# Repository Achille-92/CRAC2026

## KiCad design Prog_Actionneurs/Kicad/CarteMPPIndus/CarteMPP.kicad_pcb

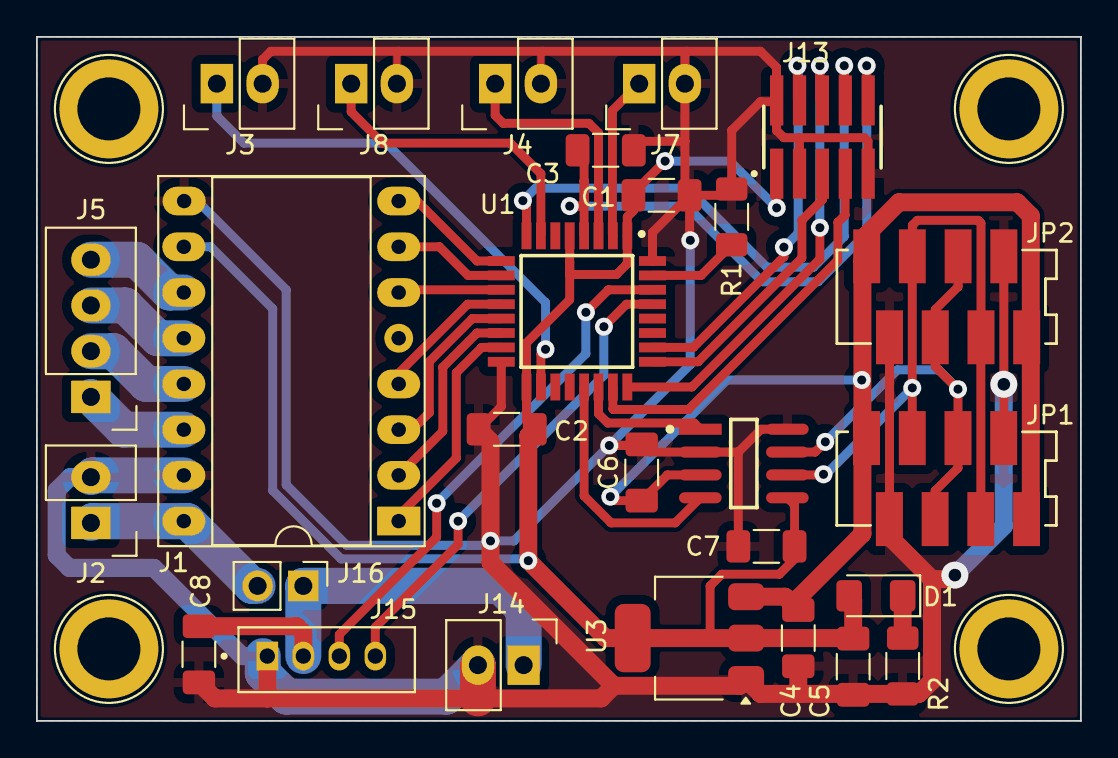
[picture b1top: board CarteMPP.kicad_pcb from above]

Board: 2 copper layers, 58.0 x 38.0 mm, 31 parts (0 on the bottom side), 34 nets.

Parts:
C1, C2, C3, C6, C7: 100nF; C_1206_3216Metric_Pad1.33x1.80mm_HandSolder
C4: 10uF; C_1206_3216Metric_Pad1.33x1.80mm_HandSolder
C5: 22uF; C_1206_3216Metric_Pad1.33x1.80mm_HandSolder
C8: Cap; C_1206_3216Metric_Pad1.33x1.80mm_HandSolder
D1: LED; LED_1206_3216Metric_Pad1.42x1.75mm_HandSolder
J1: Conn_01x08; DIP-16_W7.62mm_Socket_LongPads
J2, J3, J4, J7, J8, J14: Autocom2
J5: Autocom4
J9, J10, J11, J12: Mounting_Screw_3mm
J13: FTSH-105-01-L-DV-K; SAMTEC_FTSH-105-01-L-DV-K
J15: Conn_01x02; PinHeader_1x02_P2.54mm_Vertical
J16: Herkulex; TE_292161-4
JP1, JP2: Micromatch 8; SW_DIP_SPSTx04_Slide_9.78x12.34mm_W7.62mm_P2.54mm
R1: 10K; R_1206_3216Metric_Pad1.30x1.75mm_HandSolder
R2: 360; R_1206_3216Metric_Pad1.30x1.75mm_HandSolder
U1: STM32F303K8T6; QFP80P900X900X160-32N
U2: MCP2562FDT-E/SN; SW_DIP_SPSTx02_Slide_9.78x7.26mm_W7.62mm_P2.54mm
U3: AZ1117-3.3; SOT-223-3_TabPin2

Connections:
+3.3V: C1.2, C2.2, C5.1, C7.1, D1.2 (A), J1.10 (Pin_2), J13.01, U1.1 (VDD3), U1.5 (VDDA/VREF+), U1.17 (VDD2/VDD_USB), U2.5 (VIO), U3.2 (VO)
+5V: C4.1, C6.1, JP1.1 (VCC), JP1.8 (VCC), JP2.1 (VCC), JP2.8 (VCC), U2.3 (VDD), U3.3 (VI)
/A1: J1.12 (Pin_4), J5.3
/A2: J1.11 (Pin_3), J5.4
/Aux1: J8.1, U1.7 (PA1)
/Aux2: J3.1, U1.18 (PA8)
/Aux3: J4.1, U1.3 (PF1/PC15)
/Aux4: J7.1, U1.2 (PF0/PC14)
/B1: J1.14 (Pin_6), J5.1
/B2: J1.13 (Pin_5), J5.2
/BOOT0: R1.2, U1.31 (BOOT0/PB8/PH3)
/CAN_H: JP1.4 (CAN_H), JP1.5 (CAN_H), JP2.4 (CAN_H), JP2.5 (CAN_H), U2.7 (CANH)
/CAN_L: JP1.3 (CAN_L), JP1.6 (CAN_L), JP2.3 (CAN_L), JP2.6 (CAN_L), U2.6 (CANL)
/DIR: J1.8, U1.9 (PA3)
/EN: J1.1, U1.15 (PB1/NPOR)
/M0: J1.2, U1.14 (PB0)
/M1: J1.3, U1.13 (PA7)
/M2: J1.4, U1.12 (PA6)
/NRST: C3.2, J13.10, U1.4 (NRST)
/RX_Can: U1.21 (PA11), U2.4 (RXD)
/RX_TARGET: J13.05, U1.25 (PA15)
/Rx1: J16.3 (TXD), U1.30 (PB7)
/STBY: J1.6, U1.11 (PA5)
/STEP: J1.7, U1.10 (PA4)
/SWO: J13.04, U1.26 (PB3)
/TCK: J13.06, U1.24 (PA14)
/TMS: J13.07, U1.23 (PA13)
/TX_Can: U1.22 (PA12), U2.1 (TXD)
/TX_TARGET: J13.08, U1.8 (PA2)
/Tx1: J16.4 (RXD), U1.29 (PB6)
/V_HERKULEX: C8.2, J14.1, J15.1, J16.2 (VCC)
/V_STEPPER: J1.16 (Pin_8), J2.1, J15.2
GND: C1.1, C2.1, C3.1, C4.2, C5.2, C6.2, C7.2, C8.1, J1.9 (Pin_1), J1.15 (Pin_7), J2.2, J3.2, J4.2, J7.2, J8.2, J13.02, J13.03, J13.09, J14.2, J16.1 (GND), JP1.2 (GND), JP1.7 (GND), JP2.2 (GND), JP2.7 (GND), R1.1, R2.1, U1.16 (PB2/VSS2), U1.32 (PB8/VSS3), U2.2 (VSS), U2.8 (STBY), U3.1 (GND)
unnamed: D1.1 (K), R2.2

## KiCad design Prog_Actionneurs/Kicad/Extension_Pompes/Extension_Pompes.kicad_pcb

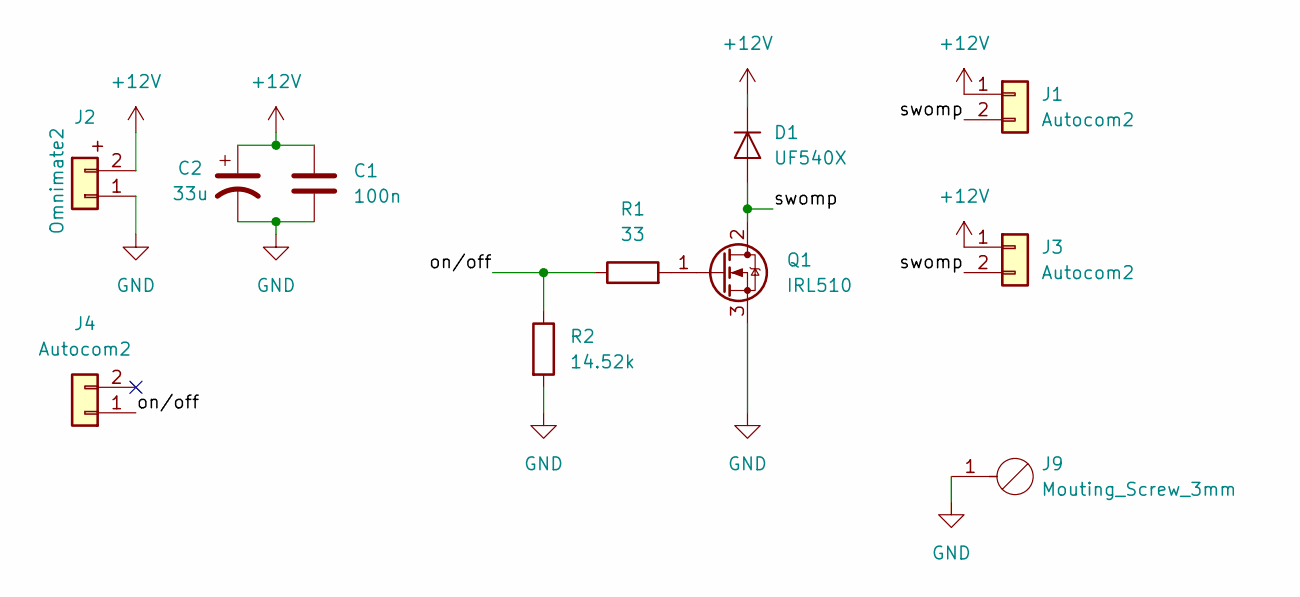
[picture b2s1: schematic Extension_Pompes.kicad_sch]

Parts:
C1: 100n; C_Rect_L7.0mm_W2.5mm_P5.00mm
C2: 33u; CP_Radial_D5.0mm_P2.50mm
D1: UF540X; D_DO-201AD_P15.24mm_Horizontal
J1, J3, J4: Autocom2
J2: Omnimate2; OmnimateSL-5,08_1x02_P5.08mm_Vertical
J9: Mouting_Screw_3mm; Mounting_Screw_3mm
Q1: IRL510; TO-220-3_Vertical
R1: 33; R_Axial_DIN0207_L6.3mm_D2.5mm_P10.16mm_Horizontal
R2: 14.52k; R_Axial_DIN0207_L6.3mm_D2.5mm_P10.16mm_Horizontal

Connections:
+12V: C1.1, C2.1, D1.1 (K), J1.1, J2.2, J3.1
/on/off: J4.1, R1.1, R2.1
/swomp: D1.2 (A), J1.2, J3.2, Q1.2 (D)
GND: C1.2, C2.2, J2.1, J9.1, Q1.3 (S), R2.2
unnamed: Q1.1 (G), R1.2

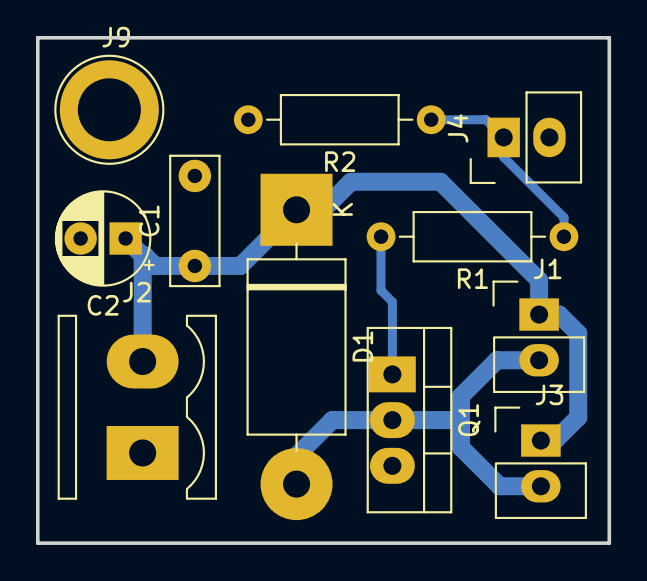
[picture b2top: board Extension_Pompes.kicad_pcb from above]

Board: 2 copper layers, 31.8 x 28.1 mm, 11 parts (0 on the bottom side), 5 nets.

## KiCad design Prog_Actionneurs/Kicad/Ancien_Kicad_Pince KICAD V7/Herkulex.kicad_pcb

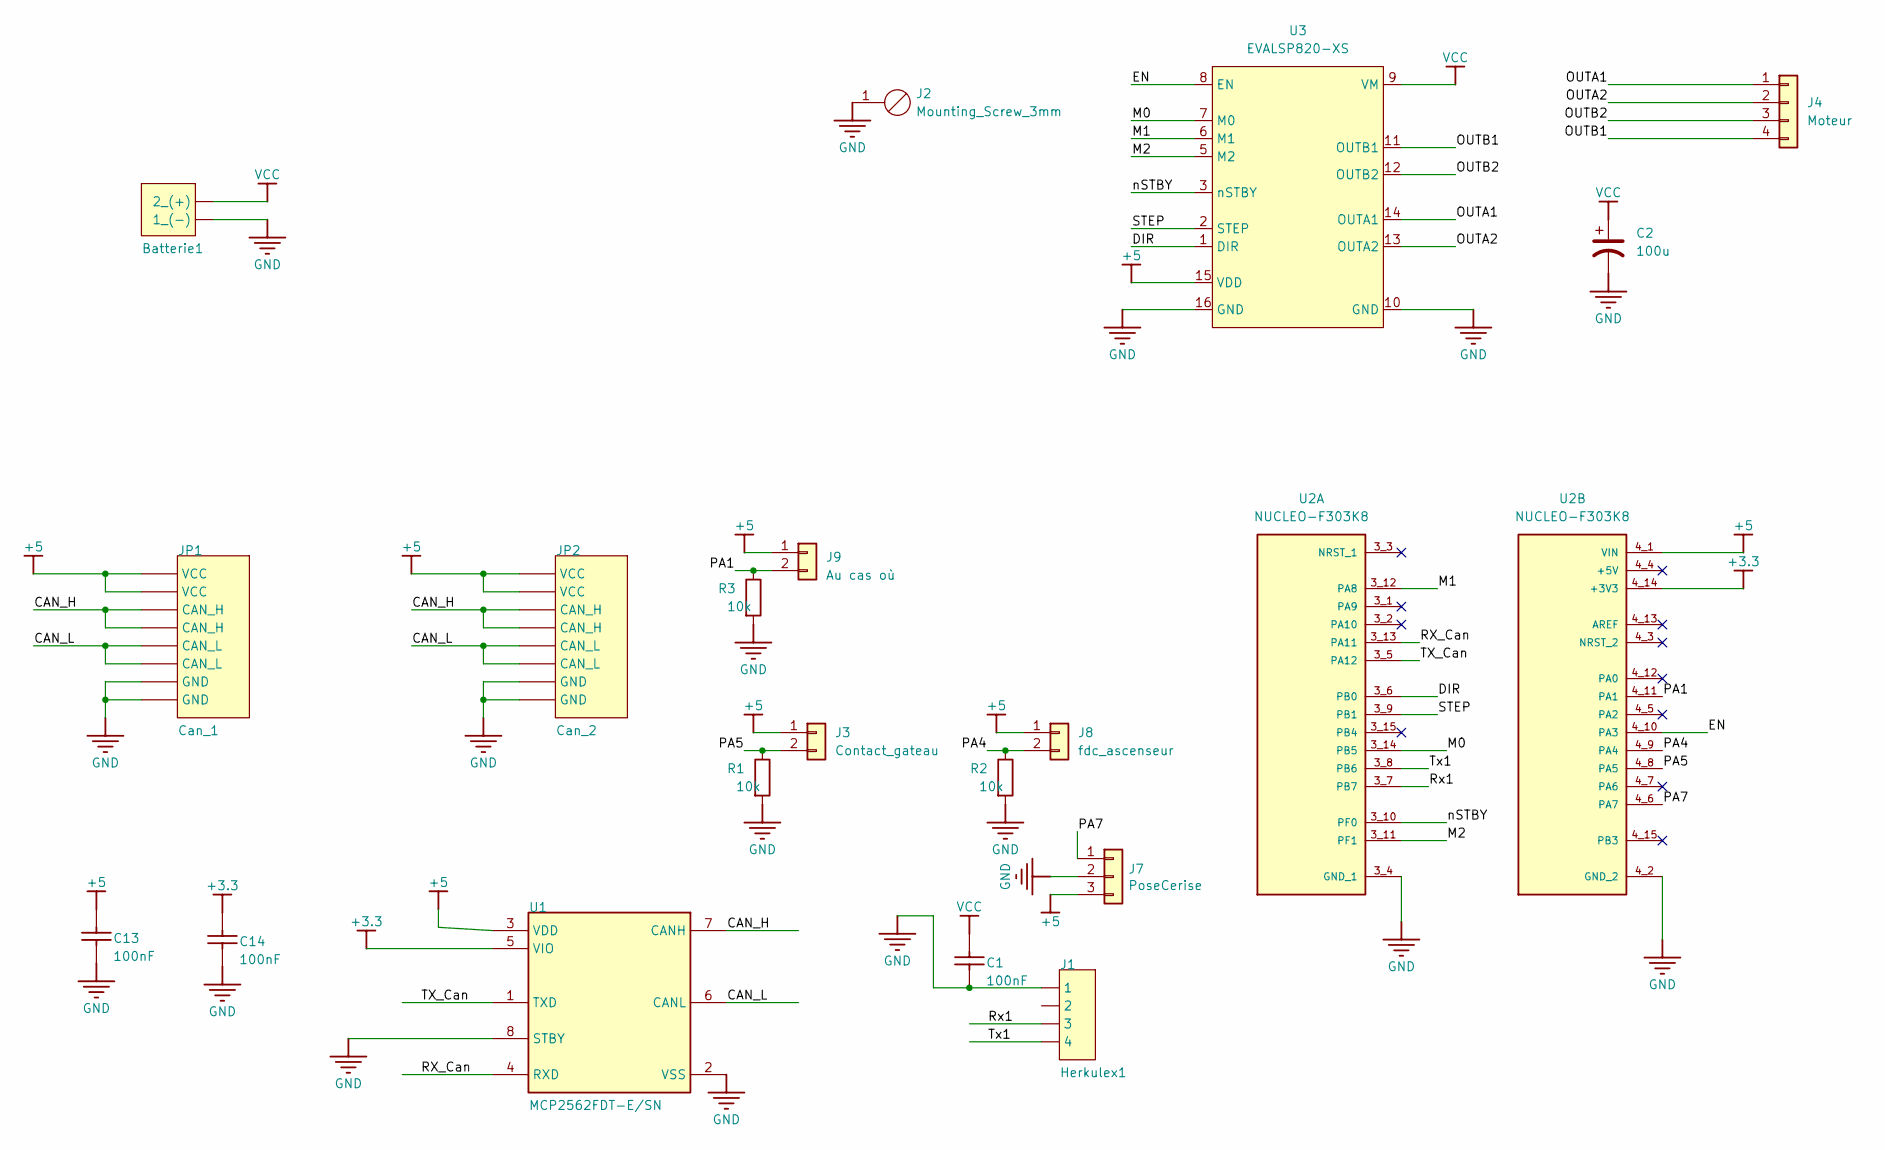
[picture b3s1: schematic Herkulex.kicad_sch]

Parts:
Batterie1: Connecteur alim 2 pts
C1: Cap
C2: 100u; CP_Radial_D10.0mm_P5.00mm
C13, C14: 100nF
J1: Herkulex1
J2: Mounting_Screw_3mm
J3: Contact_gateau; Autocom2
J4: Moteur; Autocom4
J7: PoseCerise; Autocom3
J8: fdc_ascenseur; Autocom2
J9: Au cas où; Autocom2
JP1: Can_1; MANUFACTURER PART NUMBER 7-188275-8
JP2: Can_2; MANUFACTURER PART NUMBER 7-188275-8
R1, R2, R3: 10k; R_Axial_DIN0207_L6.3mm_D2.5mm_P10.16mm_Horizontal
U1: MCP2562FDT-E/SN
U2: NUCLEO-F303K8; MODULE_NUCLEO-F303K8; PARTREV 5
U3: EVALSP820-XS

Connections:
+3.3: C14.2, U1.5 (VIO), U2.4_14 (+3V3)
+5: C13.2, J3.1, J7.3, J8.1, J9.1, JP1.1 (VCC), JP1.8 (VCC), JP2.1 (VCC), JP2.8 (VCC), U1.3 (VDD), U2.4_1 (VIN), U3.15 (VDD)
/CAN_H: JP1.4 (CAN_H), JP1.5 (CAN_H), JP2.4 (CAN_H), JP2.5 (CAN_H), U1.7 (CANH)
/CAN_L: JP1.3 (CAN_L), JP1.6 (CAN_L), JP2.3 (CAN_L), JP2.6 (CAN_L), U1.6 (CANL)
/DIR: U2.3_6 (PB0), U3.1 (DIR)
/EN: U2.4_10 (PA3), U3.8 (EN)
/M0: U2.3_14 (PB5), U3.7 (M0)
/M1: U2.3_12 (PA8), U3.6 (M1)
/M2: U2.3_11 (PF1), U3.5 (M2)
/OUTA1: J4.1, U3.14 (OUTA1)
/OUTA2: J4.2, U3.13 (OUTA2)
/OUTB1: J4.4, U3.11 (OUTB1)
/OUTB2: J4.3, U3.12 (OUTB2)
/PA1: J9.2, R3.1, U2.4_11 (PA1)
/PA4: J8.2, R2.1, U2.4_9 (PA4)
/PA5: J3.2, R1.1, U2.4_8 (PA5)
/PA7: J7.1, U2.4_6 (PA7)
/RX_Can: U1.4 (RXD), U2.3_13 (PA11)
/Rx1: J1.3, U2.3_7 (PB7)
/STEP: U2.3_9 (PB1), U3.2 (STEP)
/TX_Can: U1.1 (TXD), U2.3_5 (PA12)
/Tx1: J1.4, U2.3_8 (PB6)
/nSTBY: U2.3_10 (PF0), U3.3 (nSTBY)
GND: Batterie1.1 (1_(-)), C1.1, C2.2, C13.1, C14.1, J1.1, J2.1, J2.2 (Pin_1), J7.2, JP1.2 (GND), JP1.7 (GND), JP2.2 (GND), JP2.7 (GND), R1.2, R2.2, R3.2, U1.2 (VSS), U1.8 (STBY), U2.3_4 (GND_1), U2.4_2 (GND_2), U3.10 (GND), U3.16 (GND); also elsewhere on the board
VCC: Batterie1.2 (2_(+)), C1.2, C2.1, J1.2, U3.9 (VM)

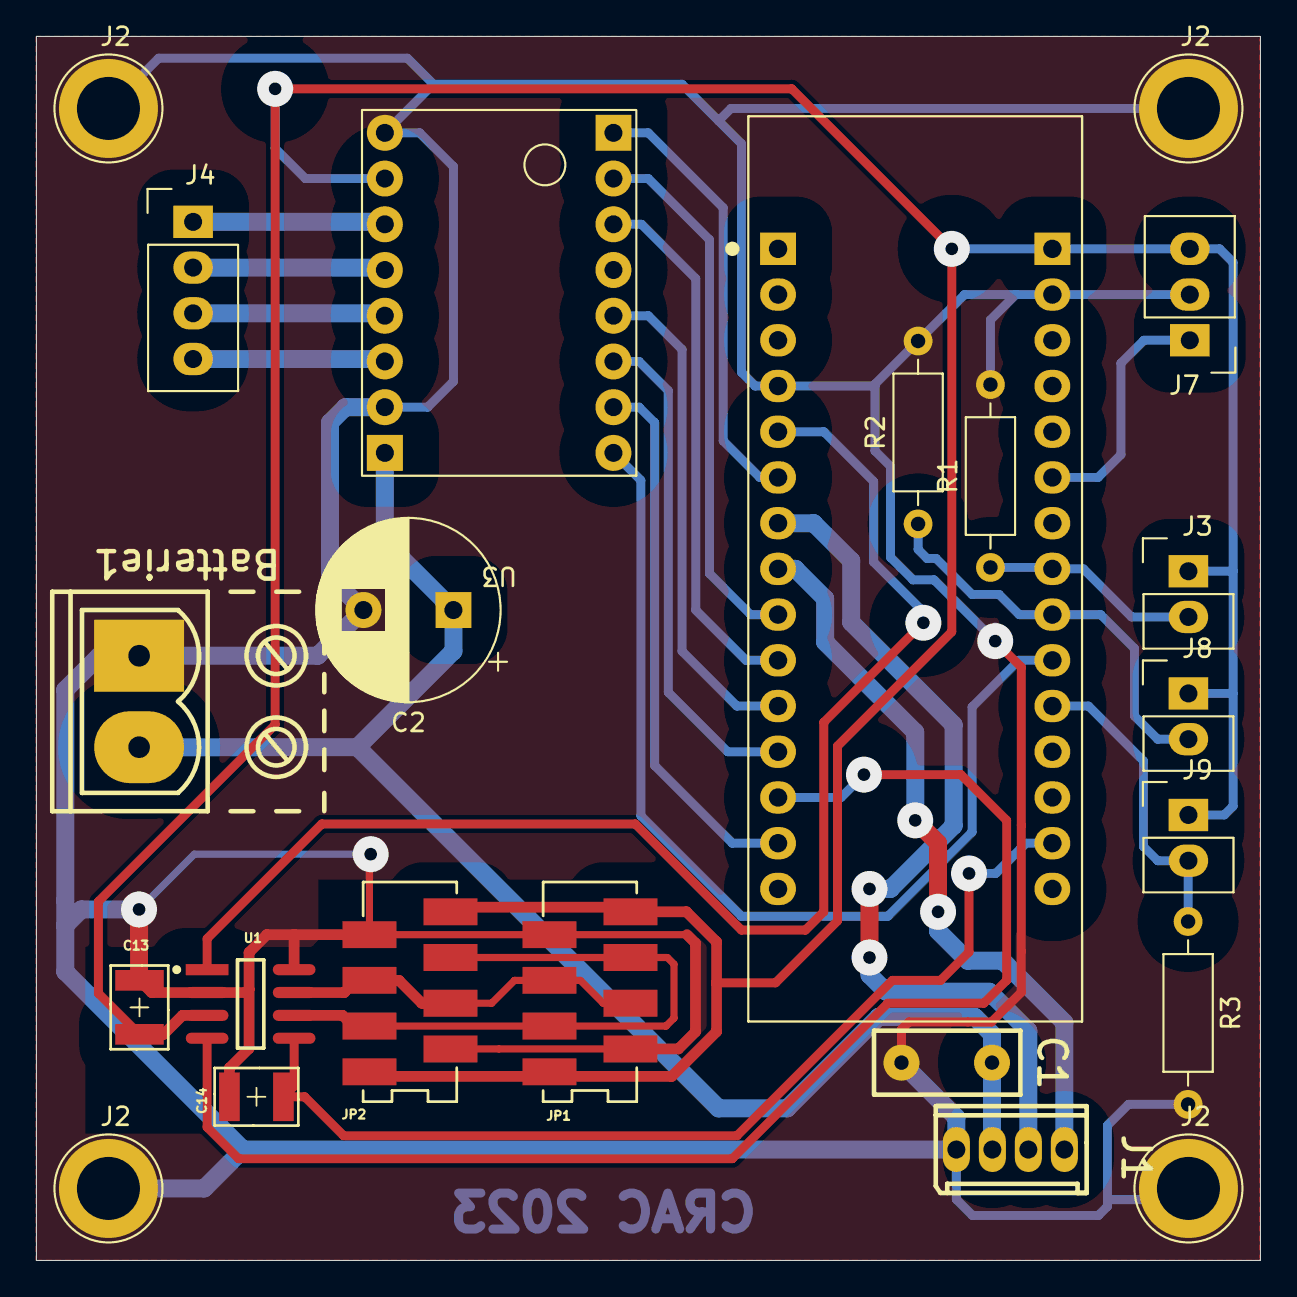
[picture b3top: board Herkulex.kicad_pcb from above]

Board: 2 copper layers, 68.0 x 68.0 mm, 23 parts (0 on the bottom side), 25 nets.

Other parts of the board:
J2#2, J2#3, J2#4: Mounting_Screw_3mm

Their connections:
GND: J2#2.4 (Pin_1), J2#3.3 (Pin_1), J2#4.1; also elsewhere on the board

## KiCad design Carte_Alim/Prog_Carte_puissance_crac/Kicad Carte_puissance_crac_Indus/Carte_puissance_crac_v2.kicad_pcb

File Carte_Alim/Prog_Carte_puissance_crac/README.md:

## Rapport

[Rapport_ERS3_Bryan_ZHANG.pdf](https://github.com/user-attachments/files/18724378/Rapport_ERS3_Bryan_ZHANG.pdf)

## KiCad de la carte

https://drive.google.com/file/d/13JI4LmcO5JpdWw6Ys9MJsPXT3uxtk39C/view?usp=drive_link

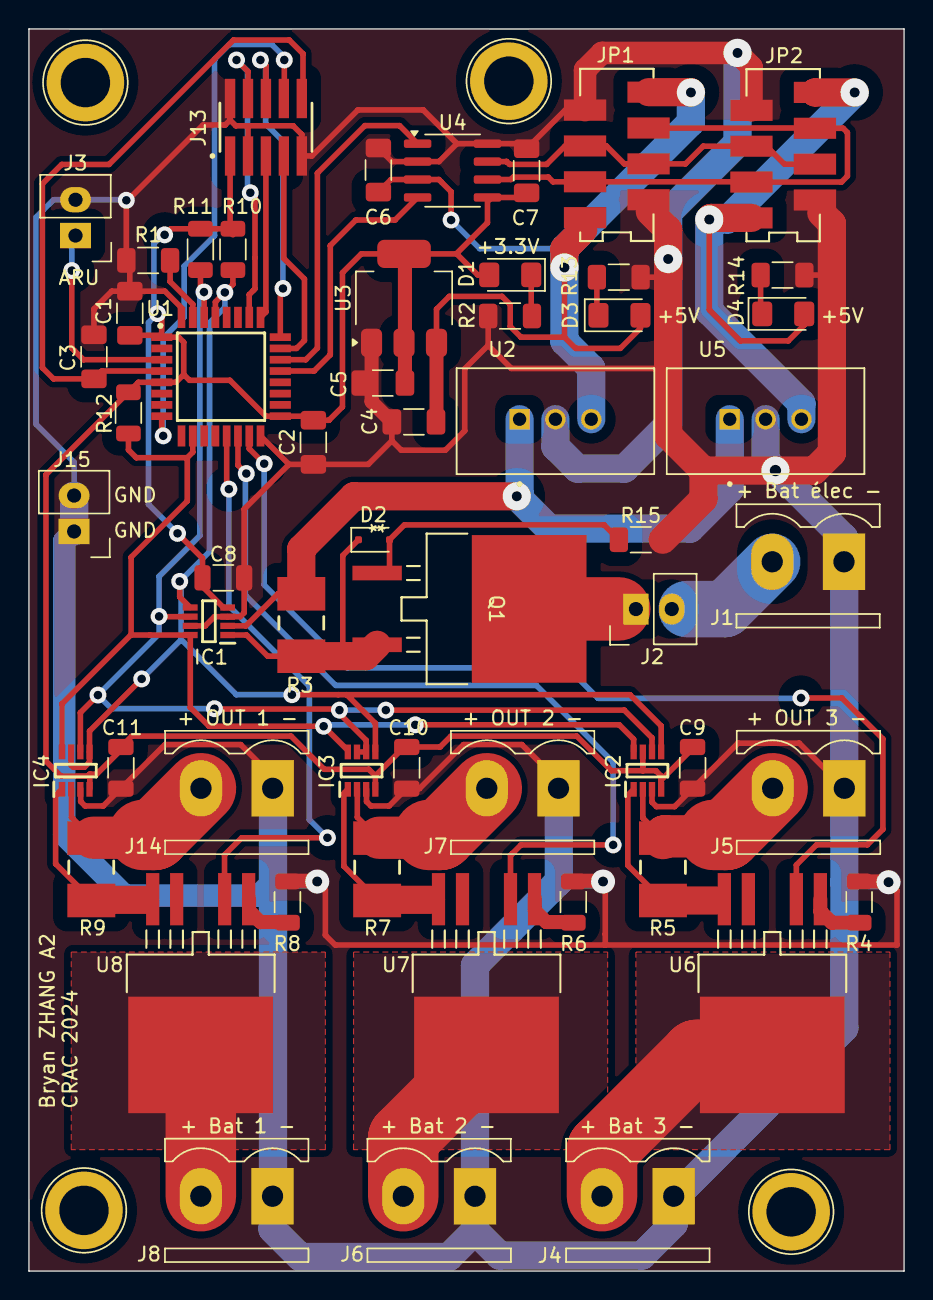
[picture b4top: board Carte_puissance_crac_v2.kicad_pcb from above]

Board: 2 copper layers, 62.0 x 88.0 mm, 60 parts (0 on the bottom side), 42 nets.

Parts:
C1, C2, C3, C6, C7: 100nF; C_1206_3216Metric_Pad1.33x1.80mm_HandSolder
C4: 10uF; C_1206_3216Metric_Pad1.33x1.80mm_HandSolder
C5: 22uF; C_1206_3216Metric_Pad1.33x1.80mm_HandSolder
C8, C9, C10, C11: 0.1µ; C_1206_3216Metric
D1, D3, D4: LED; LED_1206_3216Metric_Pad1.42x1.75mm_HandSolder
D2: D_Zener; D_SOD-323F
IC1, IC2, IC3, IC4: INA236AIDDFR; SOP65P280X110-8N
J1, J4, J5, J6, J7, J8, J14: Omnimate2; OmnimateSL-5,08_1x02_P5.08mm_Vertical
J2, J3, J15: Autocom2
J9, J10, J11, J12: Mounting_Screw_3mm
J13: FTSH-105-01-L-DV-K; SAMTEC_FTSH-105-01-L-DV-K
JP1, JP2: Micromatch 8; SW_DIP_SPSTx04_Slide_9.78x12.34mm_W7.62mm_P2.54mm
Q1: SQM40031EL_GE3; TO-236D2PAK_VIS
R1: 10K; R_1206_3216Metric_Pad1.30x1.75mm_HandSolder
R2: 360; R_1206_3216Metric_Pad1.30x1.75mm_HandSolder
R3, R5, R7, R9: CSNL2512FT5L00
R4, R6, R8: 150; R_1206_3216Metric
R10, R11, R12: R_1206_3216Metric
R13, R14: 560; R_1206_3216Metric_Pad1.30x1.75mm_HandSolder
R15: 12k; R_1206_3216Metric_Pad1.30x1.75mm_HandSolder
U1: STM32F303K8T6; QFP80P900X900X160-32N
U2, U5: TSR_2-2450; CONV_TSR_2-2450
U3: AZ1117-3.3; SOT-223-3_TabPin2
U4: MCP2562-E-SN; SOIC-8_3.9x4.9mm_P1.27mm
U6, U7, U8: BTS441TG; IC5_BTS441TG_INF

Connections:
+3.3V: C1.2, C2.2, C5.1, C7.1, C8.2, C9.2, C10.2, C11.2, D1.2 (A), IC1.4 (VS), IC2.4 (VS), IC2.7 (A0), IC3.4 (VS), IC4.4 (VS), J13.01, R10.2, R11.2, R12.2, U1.1 (VDD3), U1.5 (VDDA/VREF+), U1.17 (VDD2/VDD_USB), U3.2 (VO), U4.5 (Vio)
+5V: C4.1, C6.1, D3.2 (A), JP1.1 (VCC), JP1.8 (VCC), U2.3 (+VOUT), U3.3 (VI), U4.3 (VDD)
+5V CAN2: D4.2 (A), JP2.1 (VCC), JP2.8 (VCC), U5.3 (+VOUT)
+BAT_ELEC: J1.2, J2.2
+VBAT_1: J8.2, U8.3 (VBB)
+VBAT_2: J6.2, U7.3 (VBB)
+VBAT_3: J4.2, U6.3 (VBB)
/ALERT: IC1.8 (ALERT), IC2.8 (ALERT), IC3.8 (ALERT), IC4.8 (ALERT), R12.1, U1.10 (PA4)
/ARU: J3.1, U1.3 (PF1/PC15)
/BOOT0: R1.2, U1.31 (BOOT0/PB8/PH3)
/CAN_H: JP1.4 (CAN_H), JP1.5 (CAN_H), JP2.4 (CAN_H), JP2.5 (CAN_H), U4.7 (CANH)
/CAN_L: JP1.3 (CAN_L), JP1.6 (CAN_L), JP2.3 (CAN_L), JP2.6 (CAN_L), U4.6 (CANL)
/IN+1: IC4.1 (IN+), R9.1, U8.5 (OUT)
/IN+2: IC3.1 (IN+), R7.1, U7.5 (OUT)
/IN+3: IC2.1 (IN+), R5.1, U6.5 (OUT)
/IN+main: D2.1 (K), IC1.1 (IN+), Q1.3 (S), R3.1
/IN-1: IC4.2 (IN-), J14.2, R9.2
/IN-2: IC3.2 (IN-), J7.2, R7.2
/IN-3: IC2.2 (IN-), J5.2, R5.2
/IN-main: IC1.2 (IN-), R3.2, U2.1 (+VIN), U5.1 (+VIN)
/NRST: C3.2, J13.10, U1.4 (NRST)
/PowerSW1: U1.13 (PA7), U8.2 (IN)
/PowerSW2: U1.14 (PB0), U7.2 (IN)
/PowerSW3: U1.15 (PB1/NPOR), U6.2 (IN)
/RX_Can: U1.21 (PA11), U4.4 (RXD)
/RX_TARGET: J13.05, U1.25 (PA15)
/SCL: IC1.5 (SCL), IC2.5 (SCL), IC3.5 (SCL), IC4.5 (SCL), IC4.7 (A0), R10.1, U1.29 (PB6)
/SDA: IC1.6 (SDA), IC2.6 (SDA), IC3.6 (SDA), IC3.7 (A0), IC4.6 (SDA), R11.1, U1.30 (PB7)
/SWO: J13.04, U1.26 (PB3)
/TCK: J13.06, U1.24 (PA14)
/TMS: J13.07, U1.23 (PA13)
/TX_Can: U1.22 (PA12), U4.1 (TXD)
/TX_TARGET: J13.08, U1.8 (PA2)
GND: C1.1, C2.1, C3.1, C4.2, C5.2, C6.2, C7.2, C8.1, C9.1, C10.1, C11.1, IC1.3 (GND), IC1.7 (A0), IC2.3 (GND), IC3.3 (GND), IC4.3 (GND), J1.1, J3.2, J4.1, J5.1, J6.1, J7.1, J8.1, J13.02, J13.03, J13.09, J14.1, J15.1, J15.2, JP1.2 (GND), JP1.7 (GND), JP2.2 (GND), JP2.7 (GND), R1.1, R2.1, R4.1, R6.1, R8.1, R13.1, R14.1, R15.1, U1.16 (PB2/VSS2), U1.32 (PB8/VSS3), U2.2 (GND), U3.1 (GND), U4.2 (VSS), U4.8 (STBY), U5.2 (GND)
unnamed: D1.1 (K), R2.2
unnamed: D2.2 (A), Q1.1 (G), R15.2
unnamed: D3.1 (K), R13.2
unnamed: D4.1 (K), R14.2
unnamed: J2.1, Q1.2 (D)
unnamed: R4.2, U6.1 (GND)
unnamed: R6.2, U7.1 (GND)
unnamed: R8.2, U8.1 (GND)

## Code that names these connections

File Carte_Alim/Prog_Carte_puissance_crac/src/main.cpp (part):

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#include "INA236.h"
#include "ID_CAN.h"

#define PINARU PF1   // D8
#define PINALERT PA4 // A3
// attention interrupteur 1 et 3 inversée sur la sérigraphie PIN par rapport au schéma sur kicad
// pins par rapport a la sérigraphie
#define PININTERRUPTEURBATT1 PA7     // D6
#define PININTERRUPTEURBATT2 PB0     // D3
#define PININTERRUPTEURBATT3 PB1     // A6
#define TENSION_CELLULE_DECHARGE 1.1 // Seuil d'une cellule est déchargé
#define TENSION_CELLULE_CHARGE 1.4   // tension pour laquelle une cellule est bien chargé
// Adresses Capteurs des batteries
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INA236 Batterie2(ADRESSE_CAPT2);
INA236 Batterie3(ADRESSE_CAPT3);

STM32_CAN Can1(CAN1, DEF); // Utilise les broches PA11/12 pour CAN1.3#
static CAN_message_t CAN_TX_msg;
static CAN_message_t CAN_RX_msg;

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
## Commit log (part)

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2026-01-07 Update ProgrammeTest
2026-01-08 Update Deplacement + traj base lidar
2026-01-08 MAJ Déplacement SANS Stratégie
2026-01-08 Adjust robot movement parameters and strategy settings
2026-01-08 Simplify trajectory handling and remove unused code
    Refactor trajectory calculation and update logic.
2026-01-08 Create base lidar safe sans CAN points
2026-01-11 Nouveau Astars
2026-01-13 Nouveau Astars, No Strategie
2026-01-14 MAJ Rotation
2026-01-14 MAJ Batteries
2026-01-14 Refactor ProgrammeTest for improved readability
2026-01-14 Update MessageErreur
2026-01-14 Test Unitaire Rotation
2026-01-14 Test Unitaire Astars (Avec Rotation et Reculer)
2026-01-15 MAJ Batteries
    Affichage texte %Bat en rouge si alerte
2026-01-15 Test co ennemi + angle
    Objectif : supprimer le thread inutil
    Ajout :
    - moyennage des coordonnées dans le thread Lidar
    - angle_ennemi quand mvt_ennemi supérieur à seuil
2026-01-16 Rotation et Reculer fonctionne
    Updated color variable and Lidar settings. Adjusted enemy coordinates and added logic for calculating enemy position.
2026-01-18 Nouvelle Version calcul Ennemi
2026-01-20 Modify parameters and conditions in ProgrammeTest
    Updated various parameters and conditions in ProgrammeTest, including changing 'Reel' to True, adjusting sleep duration, and modifying buffer size.
2026-01-20 Refactor lidar point calculation and improve readability
2026-01-20 Nouvelle Strat pré-définie
    Nouveaux points
    Simul Bouton Attraper
    Avancer + Consigne : Tolérance
2026-01-21 Nouvelle Strat pré-définie
2026-01-22 Toggle Lidar_on setting to False
    Changed Lidar_on setting from True to False.
2026-01-22 Update message sending for movement and angle verification
    Refactor message sending logic based on movement, angle, and recalibration checks.
2026-01-23 Implement action deletion control flag
    Added a flag to control action deletion in the process.
2026-01-23 Modify robot dimensions and action parameters
    Updated robot dimensions and adjusted action list parameters.
2026-01-26 Il faut prendre en compte les moments où on récupère ou pas
2026-01-26 Plus aucun GM
2026-01-26 test
2026-01-27 Astar en Thread
2026-01-28 Refactor battery control constants and update CAN messages
2026-01-28 Batteries fonctionne sauf 3eme en mode Test
2026-01-31 ajout matrice anti distorsion
2026-02-01 Ajout Point intermédiaire en cas de grosse ligne droite
2026-02-02 Suppr PAMI, retour au nid
2026-02-02 Mise en place Init Cartes + BAU, avancement Sécurité Pinces : faire Retourner et Relacher
2026-02-03 Ajout fichier_strategie.py
2026-02-03 Programme mis au propre
2026-02-03 Commentaires cleans
2026-02-04 Détection robot adverse
2026-02-06 Ajout choix de la couleur de l'équipe
2026-02-06 Ajout Debug_Action
2026-02-06 Pour Stratégie = True, ajout des points d'arrivée automatique pour les Noisettes à l'horizontale. Verticales : marche pas, Astar a du mal
2026-02-07 Remplissage "Liste_actions" pour Attraper, bug avec Astar
2026-02-08 Postionnement bons, Astar mache, Affichage Noisettes dans robot (affichage.py à modifier), pas de Retourner ni GM
2026-02-08 Ajout retourner, pas parfait
2026-02-09 Début de dépôt GM, uniquement sans Noisette dans GM, et sous_pince == 12, pas de pince Avant/arrière
2026-02-10 Ajout Actionneurs
2026-02-11 GM fait pour sous_pince, pas fait pour Noisette déjà dans GM. Bug, robot recule pas assez pour GM en bas
2026-02-12 Ajout Projet Platerfom.io CAN pour Actionneur
2026-02-12 verif_action et recevoir action marchent
2026-02-12 Prêt pour tester les Actionneurs
2026-02-13 Version Caméra + Stratégie
    Added enemy zone security features and updated display initialization.
2026-02-17 Prêt pour tester Carte Batteries : 3 Batteries + Alertes + Interrupteurs + BAU + état carte
2026-02-18 Update print statement from 'Hello' to 'Goodbye'
2026-02-18 Modify CAN ID list and update data handling
    Updated the list of IDs for CAN reception and modified data unpacking logic for battery states and RPI state. Added sending logic for battery switch states.
2026-02-18 Refactor loop function and update CAN messages
    Refactor loop function and update CAN message sending.
2026-02-19 Ajout Programme STM32 Carte Batteries
2026-02-19 Modif Nom dossier CarteAlim
2026-02-20 Prêt pour test Actionneur CAN
2026-02-20 Enable action simulation and update stored hazelnuts
2026-02-20 Update battery and ID lists in ProgrammeTest
2026-02-20 Refactor battery management logic and filters
2026-02-20 Add header file and define constants for battery states
2026-02-20 Add RPI_decharge flag and update conditions
2026-02-22 Association Noisette aveugle avec Noisette cam
2026-02-23 Tester Jack
2026-02-23 Programme Prêt pour tester Jack + Pince
2026-02-24 Refactor MessageErreur and add error handling
    Removed preprocessor definitions for various constants related to battery and robot control. Added error handling for unpacking data in the LectureCAN function.
2026-02-24 Refactor action list and print statements
    Updated action list and modified print statements for better clarity.
2026-02-25 Camera, Sans WiFi
2026-02-25 WiFi : BC vers Robot
2026-02-25 WiFi
2026-02-25 WiFi fonctionne dans les deux sens
2026-02-25 Pince fonctionne, Jack fonctionne, WiFi fonctionne dans les deux sens
2026-02-26 Sortie périmètre ennemi, fréquence affichage
2026-02-27 Nouveaux noms IP
2026-02-27 test ports
2026-02-27 test ports WiFi
2026-03-01 RPI decharge False pour Bat_Compet True, j'ai enlevé les Noisettes_groupees de 4
2026-03-04 Ajustement Stratégie
2026-03-06 Réglagle bug Stratégie Retourner, Départ Coller au grenier, sortir zone interdite
2026-03-07 Modif dimensions robot, ajout Stratégie GM
2026-03-09 Début de dépôt dans le nid
2026-03-09 Update Deplacement Rémy
2026-03-09 Prêt pour tester Mouvements
2026-03-09 Bug Strat Nid : crash si Strat dans nid et pas de Noisettes dans le robot : réglé
2026-03-10 J'ai enlevé le recalage
2026-03-10 CAN : Déplacements simplifiés
2026-03-12 Update LIDAR buffer size and robot position handling
    Increased LIDAR buffer size and updated robot position variables for calculations.
2026-03-12 Implement A* trajectory calculation with threading
    Added functions for A* trajectory calculation and threading.
2026-03-12 Début d'intégration de Astar en Thread
2026-03-13 Update error message for RPLidarException
2026-03-13 Enable Lidar and adjust robot angle for start
2026-03-13 Nouveau Lidar à tester
2026-03-16 test nouveau lidar
2026-03-16 test nouveau lidar en cours
2026-03-18 test Pince + Mouv
2026-03-18 Coordonnées initiales envoyées avant le Jack
2026-03-18 Coordonnées de départ comme avant, sinon bug et pas pratique dans la carte asserv
2026-03-18 BAU dans attente Jack
2026-03-18 Init bien
2026-03-19 Ajout premier affichage des Noisettes
2026-03-19 2 pinces fonctionnent, amélioration stratégie déplacement
2026-03-20 Astar Thread qqlq bug mais fonctionne, arangement des variables en haut du programme
2026-03-20 modif ordre_mouv
2026-03-23 Tester les 2 pinces
2026-03-24 modif TOL_CAM_NOISETTE
2026-03-25 Ajout coefficient de correction caméra en X, caméra côté jaune
2026-03-26 Modif affichage des infos sur la BC
2026-03-26 Enlever print dans homographie_couleur
2026-03-26 BC : temps PAMI
2026-03-26 Ajout timer dans BC en lien avec le Robot
2026-03-27 Wifi pour PAMI
2026-03-27 Modif Stratégie
2026-03-27 modif temps BC et affichage match id
2026-03-29 Modif Astar avec Lidar
2026-03-30 test Lidar + Astar
2026-03-30 Sortir départ
2026-03-30 modif arrivée dans GM
2026-03-31 Modif Stratégie : Pas de recul après Noisette si prochaine stratégie = Noisette
2026-03-31 mode_attraper bon pour après GM
2026-04-01 lancement des cartes
2026-04-01 Ajout vérif distance pour mouvement
2026-04-01 Modif logique Astar
2026-04-01 modif Astar pas finies
2026-04-01 tests pour s'échapper du robot adverse
2026-04-02 J'ai enlevé le déplacement de l'ennemi
2026-04-02 début d'ajout recalage au départ
2026-04-03 ajout recalage initial, modif coordonnées de départ, while principal plus de Liste_actions dans la condition
2026-04-03 Ajout print pendant le recaalage, et variable On Off Recalage
2026-04-03 Attente init actionneurs après envoi RPI = 1, ajout BAU pendant recalage
2026-04-03 Modif coordonnées de départ, de sorti grenier, et de retour
2026-04-03 Modif distance pour dépôt GM
2026-04-03 Pour fin du match, l'action de stratégie se termine quand même, coordonnées de départ donc sortir grenier désactiver
2026-04-03 Début ajout curseur dans Liste_actions au début
2026-04-05 Ajout de la strat actuelle remise à la fin
2026-04-05 Ajout de la strat actuelle mise à la fin si échec, et sortie de case interdite plus loin
2026-04-05 Recul ennemi avec gestion de la direction mais sans verif grille, anglre robot mieux en simu
2026-04-06 Tentative d'ajout de verif grille mais sans direction
2026-04-07 strat gm
2026-04-08 GM plus propre
2026-04-09 modif bc : robot détectés en dehors du plan, rectangle derrière texte
2026-04-09 modif ordre tag calibration
2026-04-10 ajout envoi point suivant et après suivant
2026-04-10 RPI qui fait verif_mouv
2026-04-12 bug fix : action n'était pas supprimée lors de l'échapement du robot adverse
2026-04-13 modif endroit dépôt GM bords
2026-04-13 Stratégie débute après Noisette toutes reconnues à l'init
2026-04-14 intégration Lidar S2
2026-04-15 enlever affichage sur RPI, modif coordonnées ennemis sur BC
2026-04-15 bug caméra fermée
2026-04-15 modif stratégie pinces cassées
2026-04-15 modif retourner presque bon, problème dans mode_attraper
2026-04-15 Retourner optimiser : à tester IRL
2026-04-16 Lidar fonctionne un peu : perte d'octet, juste Lidar en Process
2026-04-16 CPU alléger
2026-04-19 modif longueur robot, début ajout MAJ Noisette
2026-04-19 curseur prêt à être tester
2026-04-19 moins d'actions pour relacher dans GM qui n'avait pas encore de Noisettes, modif mode_attraper
2026-04-21 modif pour Rémy : TOL_PRECIS/PAS, Curseur (avec ack), modif Strategie
2026-04-25 remise temps normal
2026-04-25 ajout compil + lancement progLidar.c
2026-04-25 Lidar fonctionne presque, ajout var "affichage"
2026-04-25 Lidar fonctionne, delai d'une seconde
2026-04-27 Symétrie côté Jaune à tester
2026-05-01 Lidar : détection robot adverse fonctionne peut-être pas si robot en mouvement
2026-05-02 HOMOLOGATION OK, LIDAR FONCTIONNE
2026-05-02 Ajout pousser Ninja, réduction de la zone interdite autour du grenier
2026-05-03 modif coordonnées retour
2026-05-03 bug de MAJ stratégie à cause du curseur : réglé
2026-05-03 tentative d'ajout de strat agressive, clean code
2026-05-04 MIN_CLEARANCE = 2.0 au lieu de 3.0, strat agressive des 2 côtés
2026-05-04 mode_attraper était déclenché pour Retourner puis GM
2026-05-05 modif calibration plan Noisette
2026-05-07 recalcul_traj si robot trop proche d'adverse, demande nouvelle strat si adverse bloque objectif
2026-05-08 refonte de la logique de déplacement, d'évittement, de nouvelle strat (curseur delete btw)
2026-05-09 modif association couleur WiFi
2026-05-09 stratégie : pousser GM
2026-05-10 modif association couleur
2026-05-10 MIN_CLEARANCE = 3.0, clean code stratégie GM
2026-05-10 clean code print
2026-05-10 X/Y cam robot, modif envoi CAN pour Actionneurs
2026-05-10 bug réglé : vérif angle ajoutée pour aller attraper Noisette si robot très proche
2026-05-11 BC : modif PORT PAMI
2026-05-11 delai entre chaque envoi PAMI
2026-05-12 modif strat passive
2026-05-12 modif coordonnées de départ
2026-05-12 modif mineures
2026-05-13 recalage intégrer : à tester
2026-05-13 homologation
2026-05-13 Lidar en cours
2026-05-13 Lidar : homologué, R_ENNEMI = 350
2026-05-14 modif stratégie recalage : à tester
2026-05-14 après 1er match : recalage + curseur
2026-05-14 on retourne plus car pas de couleur cam
2026-05-14 programme pour match N°2
2026-05-14 UDP PAMI dans gros robot
2026-05-14 caméra en cours
2026-05-14 BC : nouvelle détection des Noisettes
2026-05-14 couleurs non bloquantes
2026-05-14 bug corrigé : retour sans Astar si vient de déposer
2026-05-15 Robot et BC prêts pour match n°4
2026-05-15 tentative de pousser
2026-05-16 modif recalage Y
